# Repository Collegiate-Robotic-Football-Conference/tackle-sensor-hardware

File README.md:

# Collegiate Robotic Football Tackle Sensor Hardware

## Cloning the Repo

Open a git bash terminal in the directory of your choosing and call the following command:

`git clone https://github.com/Collegiate-Robotic-Football-Conference/tackle-sensor-hardware.git`

## Developing

This project was created using KiCad v6.  This must be installed prior to editing the project.

## Additional Links

- The firmware for the sensor can be found here: https://github.com/Collegiate-Robotic-Football-Conference/tackle-sensor-firmware
- An example web-serial configuration utility can be found here: https://github.com/Collegiate-Robotic-Football-Conference/tackle-sensor-utility

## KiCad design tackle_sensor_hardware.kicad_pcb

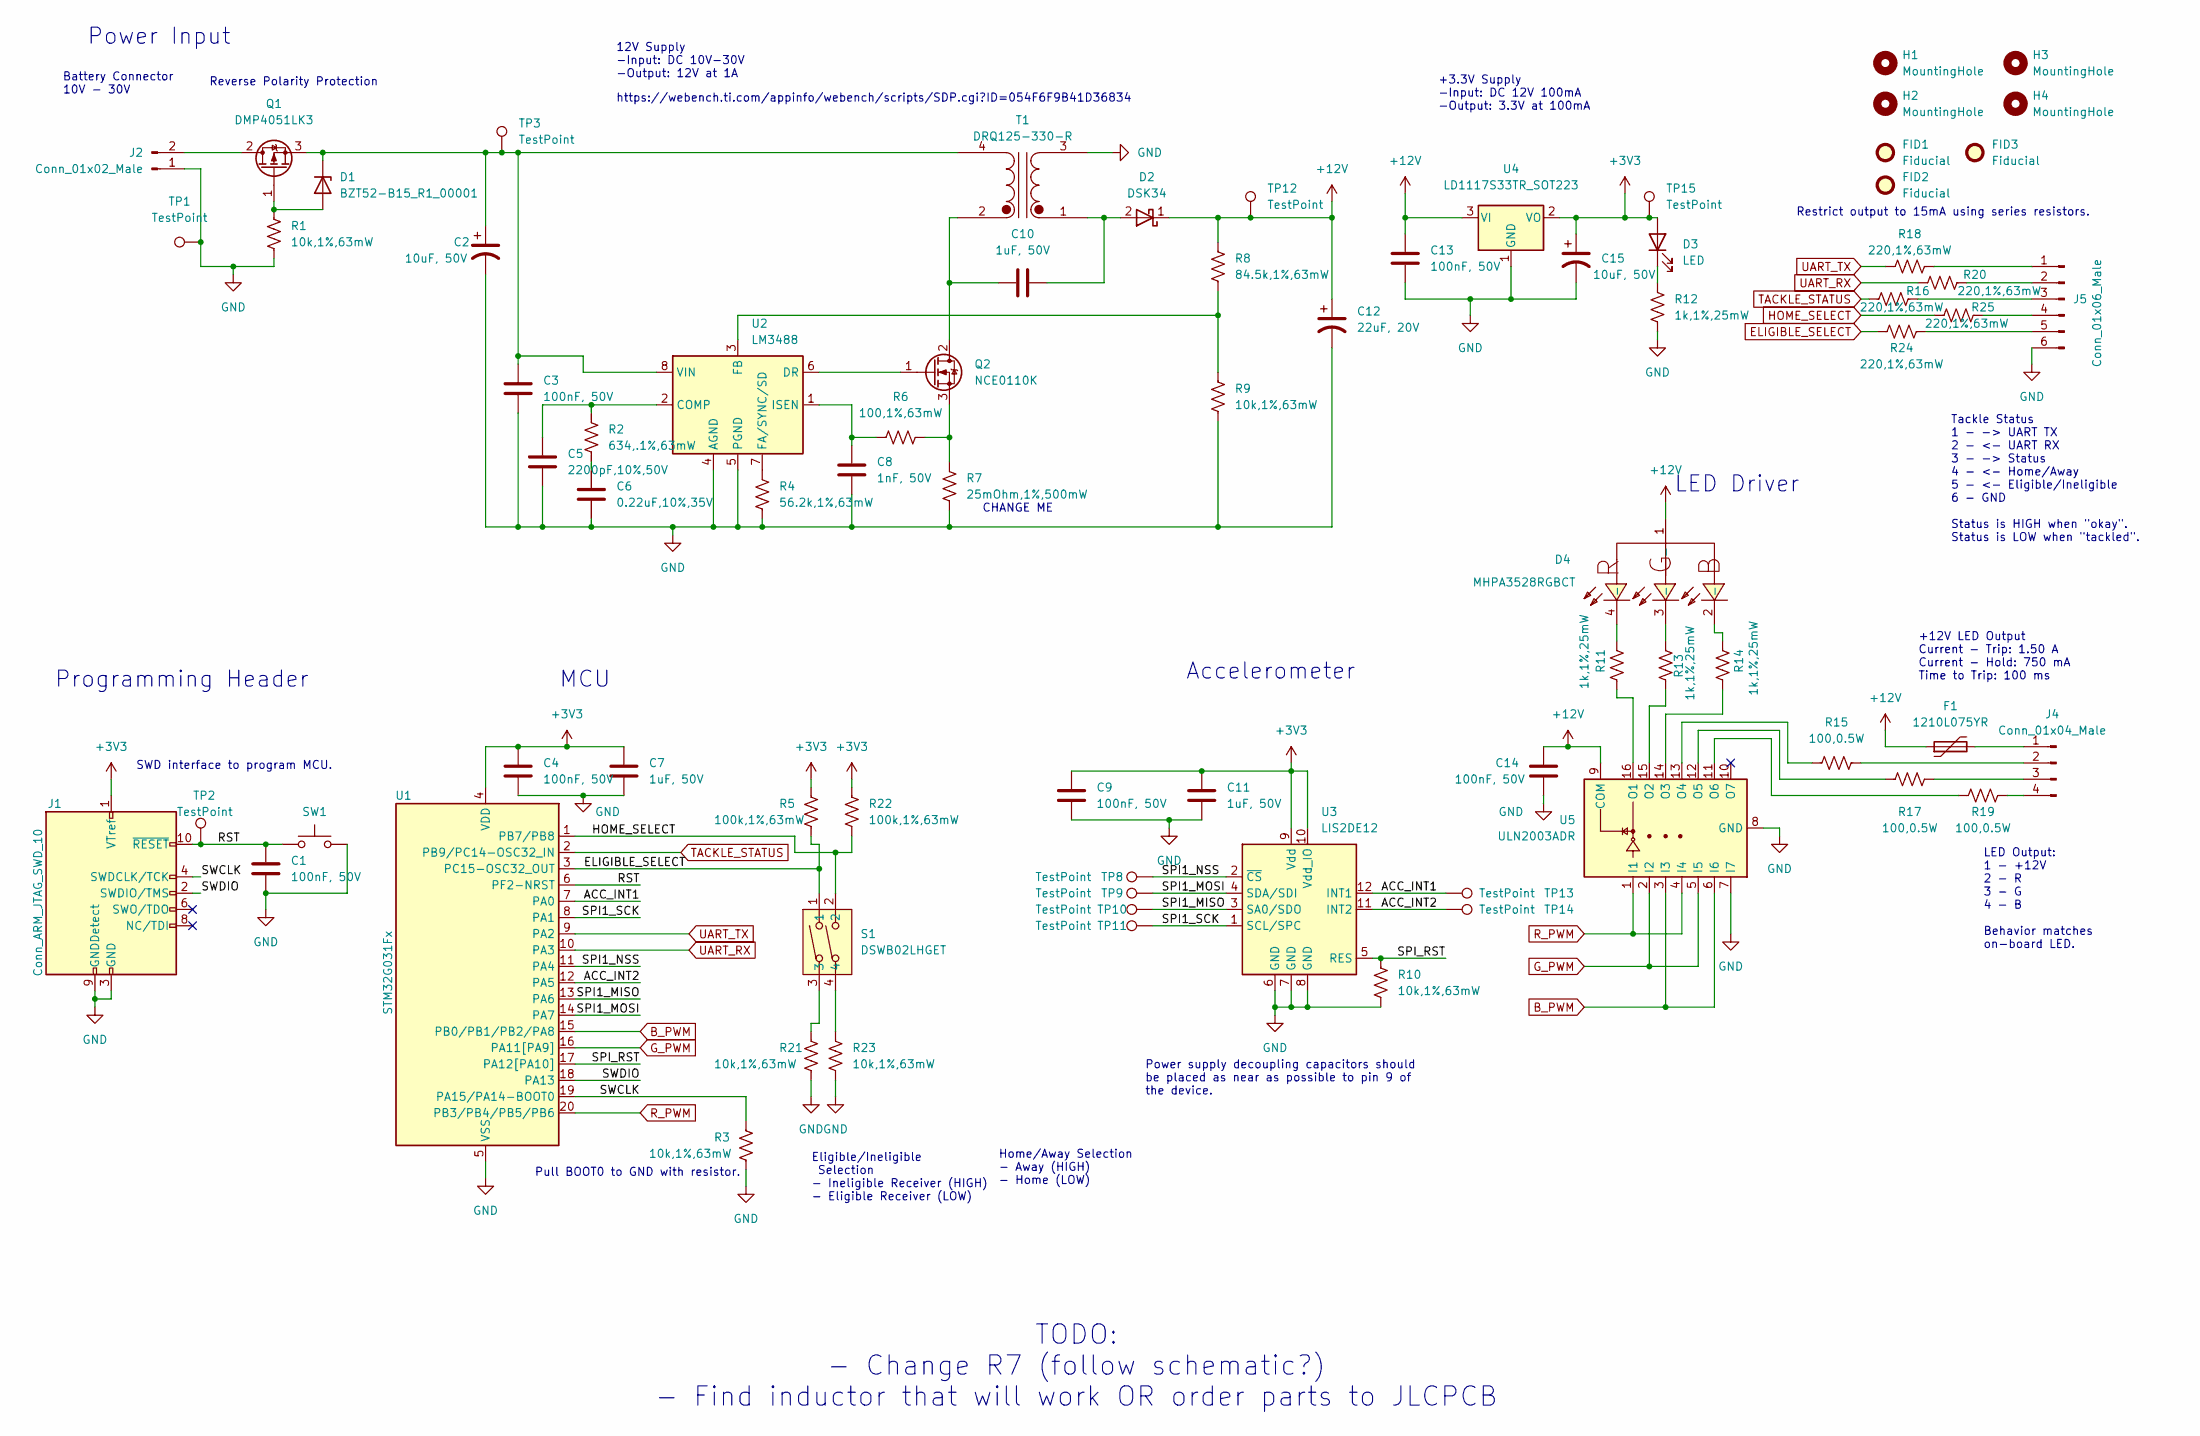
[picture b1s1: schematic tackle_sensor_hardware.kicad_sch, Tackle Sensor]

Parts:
C1, C3, C4, C9, C13, C14: 100nF, 50V; C_0805_2012Metric; MPN CC0805KRX7R9BB104; JLCPN C5137467
C2, C15: 10uF, 50V; CP_Elec_6.3x5.8; MPN UUD1H100MCL1GS; JLCPN C128459
C5: 2200pF,10%,50V; C_0402_1005Metric; MPN 0402B222K500CT; JLCPN C915853
C6: 0.22uF,10%,35V; C_0402_1005Metric; MPN CGA2B1X7R1V224KT000F; JLCPN C694490
C7, C10, C11: 1uF, 50V; C_0603_1608Metric; MPN 0603B105K500NT; JLCPN C5199872
C8: 1nF, 50V; C_0402_1005Metric; MPN 0402B102K500NT; JLCPN C106205
C12: 22uF, 20V; CP_Elec_6.3x5.9; MPN 20SVP22M; JLCPN C51953338
D1: BZT52-B15_R1_00001; D_SOD-123; MPN BZT52-B15_R1_00001; JLCPN C2932746
D2: DSK34; D_SOD-123F; MPN DSK34; JLCPN C727076
D3: LED; LED_0603_1608Metric; MPN 19-213/Y2C-CQ2R2L/3T(CY); JLCPN C84268
D4: MHPA3528RGBCT; LED-ARRAY-SMD_4P-L3.5-W2.8-TL; MPN MHPA3528RGBCT; LCSC Part C409779
F1: 1210L075YR; R_1210_3225Metric; MPN 1210L075YR; JLCPN C70097
FID1, FID2, FID3: Fiducial; Fiducial_0.5mm_Mask1.5mm
H1, H2, H3, H4: MountingHole; MountingHole_3.2mm_M3
J1: Conn_ARM_JTAG_SWD_10; 20021121-00010C4LF; MPN 20021121-00010C4LF; JLCPN C41376037
J2: Conn_01x02_Male; JST_XH_B2B-XH-A_1x02_P2.50mm_Vertical; MPN B2B-XH-A(LF)(SN); JLCPN C158012
J4: Conn_01x04_Male; JST_XH_B4B-XH-A_1x04_P2.50mm_Vertical; MPN B4B-XH-A(LF)(SN); JLCPN C144395
J5: Conn_01x06_Male; JST_XH_B6B-XH-A_1x06_P2.50mm_Vertical; JLCPN C144397
Q1: DMP4051LK3; TO-252-2; MPN DMP4051LK3-13; JLCPN C397952
Q2: NCE0110K; TO-252-2; MPN NCE0110K; JLCPN C95272
R1, R3, R9, R10, R21, R23: 10k,1%,63mW; R_0402_1005Metric; MPN 0402WGF1002TCE; JLCPN C2906861
R2: 634,.1%,63mW; R_0402_1005Metric; MPN FRC0402F6340TS; JLCPN C2998183
R4: 56.2k,1%,63mW; R_0402_1005Metric; MPN 0402WGF5622TCE; JLCPN C5126096
R5, R22: 100k,1%,63mW; R_0402_1005Metric; JLCPN C2906859
R6: 100,1%,63mW; R_0402_1005Metric; MPN 0402WGF1000TCE; JLCPN C2906860
R7: 25mOhm,1%,500mW; R_1206_3216Metric; MPN RL12FTNR200; JLCPN C160920
R8: 84.5k,1%,63mW; R_0402_1005Metric; MPN CR0402FF8452G; JLCPN C2998184
R11, R12, R13, R14: 1k,1%,25mW; R_0603_1608Metric; MPN 0603WAF1001T5E; JLCPN C2907002
R15, R17, R19: 100,0.5W; R_1210_3225Metric; MPN 1210W2F1000T5E; JLCPN C620661
R16, R18, R20, R24, R25: 220,1%,63mW; R_0402_1005Metric; MPN 0402WGF2200TCE; JLCPN C2909336
S1: DSWB02LHGET; SW-TH_DSWB02LHGET; MPN DSWB02LHGET; LCSC Part C99421
SW1: PTS645SL43SMTR92 LFS; SW_SPST_PTS645; MPN PTS645SL43SMTR92LFS; JLCPN C7470150
T1: DRQ125-330-R; DRQ125-150-R; MPN DRQ125-330-R; JLCPN C3273455
TP1, TP3, TP12, TP15: TestPoint; TestPoint_Pad_D1.0mm
TP2, TP8, TP9, TP10, TP11, TP13, TP14: TestPoint; test_point
U1: STM32G031Fx; TSSOP-20_4.4x6.5mm_P0.65mm; MPN STM32G031F8P6; JLCPN C529334
U2: LM3488; VSSOP-8_3.0x3.0mm_P0.65mm; MPN LM3488MM/NOPB; JLCPN C80773
U3: LIS2DE12; LGA-12_2x2mm_P0.5mm; MPN LIS2DE12TR; JLCPN C189624
U4: LD1117S33TR_SOT223; SOT-223-3_TabPin2; MPN LD1117S33TR; JLCPN C86781
U5: ULN2003ADR; SOIC-16_3.9x9.9mm_P1.27mm; MPN ULN2003ADR; JLCPN C7512

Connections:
+3V3: C4.1, C7.1, C9.1, C11.1, C15.1, D3.2 (A), J1.1 (VTref), R5.1, R22.1, TP15.1, U1.4 (VDD), U3.9 (Vdd), U3.10 (Vdd_IO), U4.2 (VO)
+12V: C12.1, C13.1, C14.1, D2.1 (K), D4.1 (-), F1.1, R8.1, TP12.1, U4.3 (VI), U5.9 (COM)
/ACC_INT1: TP13.1, U1.7 (PA0), U3.12 (INT1)
/ACC_INT2: TP14.1, U1.12 (PA5), U3.11 (INT2)
/RST: C1.1, J1.10 (~RESET), SW1.1, TP2.1, U1.6 (PF2-NRST)
/SPI1_MISO: TP10.1, U1.13 (PA6), U3.3 (SA0/SDO)
/SPI1_MOSI: TP9.1, U1.14 (PA7), U3.4 (SDA/SDI)
/SPI1_NSS: TP8.1, U1.11 (PA4), U3.2 (~CS)
/SPI1_SCK: TP11.1, U1.8 (PA1), U3.1 (SCL/SPC)
/SPI_RST: R10.1, U1.17 (PA12[PA10]), U3.5 (RES)
/SWCLK: J1.4 (SWDCLK/TCK), R3.2, U1.19 (PA15/PA14-BOOT0)
/SWDIO: J1.2 (SWDIO/TMS), U1.18 (PA13)
B_PWM: U1.15 (PB0/PB1/PB2/PA8), U5.3 (I3), U5.6 (I6)
ELIGIBLE_SELECT: R5.2, R24.1, S1.1, U1.3 (PC15-OSC32_OUT)
GND: C1.2, C2.2, C3.2, C4.2, C5.2, C6.2, C7.2, C8.2, C9.2, C11.2, C12.2, C13.2, C14.2, C15.2, J1.3 (GND), J1.5 (GND), J1.9 (GNDDetect), J2.1, J5.6, R1.2, R3.1, R4.2, R7.2, R9.2, R10.2, R12.2, R21.2, R23.2, SW1.2, T1.3 (SA), TP1.1, U1.5 (VSS), U2.4 (AGND), U2.5 (PGND), U3.6 (GND), U3.7 (GND), U3.8 (GND), U4.1 (GND), U5.7 (I7), U5.8 (GND)
G_PWM: U1.16 (PA11[PA9]), U5.2 (I2), U5.5 (I5)
HOME_SELECT: R22.2, R25.1, S1.2, U1.1 (PB7/PB8)
unnamed: C6.1, R2.2
unnamed: D1.2 (A), Q1.1 (G), R1.1
unnamed: C2.1, C3.1, D1.1 (K), Q1.3 (S), T1.4 (SB), TP3.1, U2.8 (VIN)
unnamed: C10.1, D2.2 (A), T1.1 (AA)
unnamed: D3.1 (K), R12.1
unnamed: D4.2 (-), R14.1
unnamed: D4.3 (-), R13.1
unnamed: D4.4 (-), R11.1
unnamed: J2.2, Q1.2 (D)
unnamed: F1.2, J4.1
unnamed: J4.2, R15.1
unnamed: J4.3, R17.1
unnamed: J4.4, R19.1
unnamed: J5.1, R18.2
unnamed: J5.2, R20.2
unnamed: J5.3, R16.2
unnamed: J5.4, R25.2
unnamed: J5.5, R24.2
unnamed: Q2.1 (G), U2.6 (DR)
unnamed: R21.1, S1.3
unnamed: R23.1, S1.4
unnamed: C5.1, R2.1, U2.2 (COMP)
unnamed: R4.1, U2.7 (FA/SYNC/SD)
unnamed: R8.2, R9.1, U2.3 (FB)
unnamed: C8.1, R6.1, U2.1 (ISEN)
unnamed: R11.2, U5.16 (O1)
unnamed: R13.2, U5.15 (O2)
unnamed: R14.2, U5.14 (O3)
unnamed: R15.2, U5.13 (O4)
unnamed: R17.2, U5.12 (O5)
unnamed: R19.2, U5.11 (O6)
R_PWM: U1.20 (PB3/PB4/PB5/PB6), U5.1 (I1), U5.4 (I4)
TACKLE_STATUS: R16.1, U1.2 (PB9/PC14-OSC32_IN)
UART_RX: R20.1, U1.10 (PA3)
UART_TX: R18.1, U1.9 (PA2)

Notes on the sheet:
Programming Header
Eligible/Ineligible Selection - Ineligible Receiver (HIGH) - Eligible Receiver (LOW)
LED Driver
12V Supply -Input: DC 10V-30V -Output: 12V at 1A
Home/Away Selection - Away (HIGH) - Home (LOW)
+12V LED Output Current - Trip: 1.50 A Current - Hold: 750 mA Time to Trip: 100 ms
CHANGE ME
TODO: - Change R7 (follow schematic?) - Find inductor that will work OR order parts to JLCPCB
+3.3V Supply -Input: DC 12V 100mA -Output: 3.3V at 100mA
Power Input
Tackle Status 1 - -> UART TX 2 - <- UART RX 3 - -> Status 4 - <- Home/Away 5 - <- Eligible/Ineligible 6 - GND Status is HIGH when "okay". Status is LOW when "tackled".
LED Output: 1 - +12V 2 - R 3 - G 4 - B Behavior matches on-board LED.
Pull BOOT0 to GND with resistor.
Battery Connector 10V - 30V
SWD interface to program MCU.
Restrict output to 15mA using series resistors.
MCU
Reverse Polarity Protection
Accelerometer
https://webench.ti.com/appinfo/webench/scripts/SDP.cgi?ID=054F6F9B41D36834
Power supply decoupling capacitors should be placed as near as possible to pin 9 of the device.

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
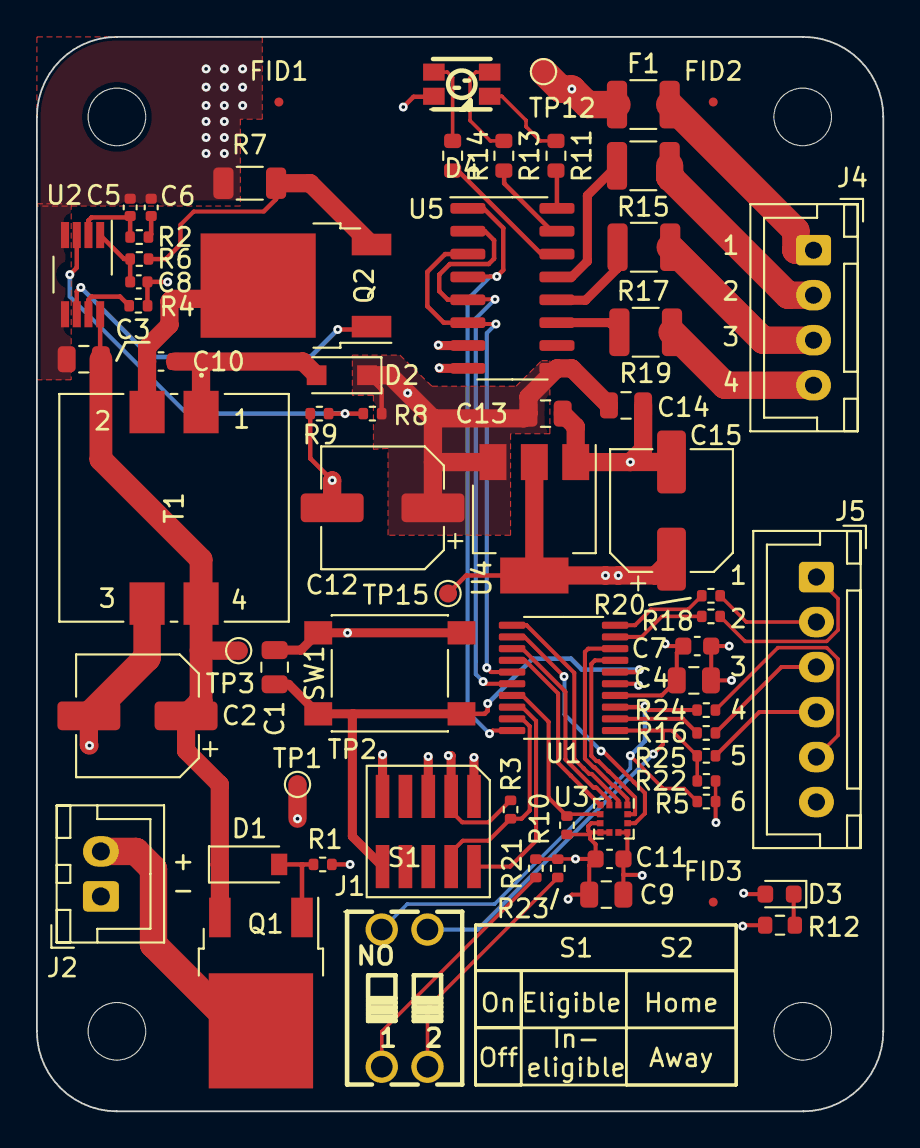
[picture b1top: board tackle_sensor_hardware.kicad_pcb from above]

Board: 4 copper layers, 47.0 x 59.7 mm, 77 parts (0 on the bottom side), 54 nets.

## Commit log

2024-09-13 - update README links
2026-05-23 REV2.1_UPLOAD
